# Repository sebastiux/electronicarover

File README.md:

# electronicarover

Electrónica del rover: Raspberry Pi 5 como cerebro, 2× ESP32 esclavas (tracción y servos) y 3× L298N para 6 motores Pololu 37D.

- [`hardware/`](hardware/README.md): PCB portadora en KiCad (esquemático, PCB, footprints propios, generador en Python).
- [`firmware/common/rover_pins.h`](firmware/common/rover_pins.h): mapa de pines de la PCB para el firmware.

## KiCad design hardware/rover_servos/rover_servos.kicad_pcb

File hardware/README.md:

# Rover Controller v1.2: PCB de 2 capas (KiCad)

> **Versión para fresar en casa en 2 tarjetas de una cara (tracción y servos):** ver [`DOS_TARJETAS.md`](DOS_TARJETAS.md). La versión de una sola tarjeta de 2 caras para la Cubiko está en [`cubiko/README.md`](cubiko/README.md).

> **Lista completa de piezas y medidas de pads y barrenos:** [`LISTA_MATERIALES.md`](LISTA_MATERIALES.md).

> **Para entender el circuito:** [`esquema_didactico/`](esquema_didactico/README.md) (4 hojas: alimentación, señales y cada tarjeta por dentro).

PCB de **2 capas** (F.Cu arriba y B.Cu abajo) de 200 × 150 mm. Los módulos se montan encima y la tarjeta los interconecta, así que los únicos cables que salen son los de **batería, motores/encoders, servos y reguladores**.

| Bloque | Módulo | Función |
|---|---|---|
| U1 | **Raspberry Pi 5**, debajo de la PCB con header hembra 2x20 | Cerebro |
| U2 | **ESP32 DevKit V1 30p** (ESP32-A, horizontal) | Tracción: 6 motores + 6 encoders |
| U3 | **ESP32 DevKit V1 30p** (ESP32-B, vertical) | 4 servos de dirección + 4 del brazo (base, hombro, pinza, codo/muñeca), voltaje de batería |
| U4–U6 | **3× L298N (HW-095)** con pines en vez de bornas | 6× Pololu 37D 12V 30:1 |
| J1 | **XT60 macho** | Batería LiPo 3S (Gens Ace 5000 mAh) |
| J3 / J4 / J5 / J6 | Borneras 5.08 mm | 12 V hacia el step-down de 5 V, 12 V hacia el BEC de servos, entrada de 5 V/5 A y entrada de servos a 6 V |
| J11–J16 + J21–J26 | Bornera + header 1x6 (cable Pololu) | Motores y encoders |
| J31–J38 | Header 1x3 (GND, V+, SIG) | Servos |

**Estado:** ruteada al 100 %. DRC de KiCad: **0 violaciones y 0 conexiones pendientes**. Además `tools/check_proto.py` confirma **0 conexiones abiertas sin barrenos metalizados**. Lleva 101 vías de 2.2/1.0 mm.

**Un solo diseño sirve para dos formas de fabricar.** La PCB se diseñó para funcionar sin metalizado; con metalizado (PTH) funciona igual.

| Fabricación | Paquete | Para quién |
|---|---|---|
| **Prototipado CNC** (sin PTH, sin máscara) | `fab/rover_controller_v1.2_prototipado.zip` | Servicio de prototipado de AG Electrónica (1 h a 1 día) |
| **Industrial + ensamble THT** | `fab/rover_controller_v1.2_PCBWay.zip` (detalle en `fab/pcbway/`) | PCBWay, llave en mano: todo soldado menos L298N y Pi |

## Cambios en la v1.2

| Cambio | Por qué |
|---|---|
| **Modo prototipado:** cada pad conecta solo por la cara donde se suelda (abajo; el header de la Pi, arriba). Las pistas de arriba van solo de vía a vía. Las vías son de 2.2/1.0 mm para meter un pin y soldarlo por ambas caras. | El servicio de prototipado no metaliza barrenos. |
| **L298N de 43.9 × 43.9 mm** con barrenos de **Ø4.0 mm a ±18.75 mm**, solo los 2 del lado del disipador | Las fuentes dan separaciones de 36.6, 37, 37.2 y 38.0 mm; un barreno de 4 mm acepta un M3 en cualquier separación entre 36.5 y 38.5 mm. El lado de los pines queda fijo por los 13 pines soldados. |
| GND de los pines 25 y 39 de la Pi con vía propia | Libera la salida del pin 29 (UART2 RX). |
| Pista de 12 V entre U4 y U6 desplazada | Deja lugar a la vía de GND de U5. |

## Cambios en la v1.1 (revisión de diseño)

| Cambio | Por qué |
|---|---|
| Retorno de **GND de potencia de 3 mm**, igual que VBAT | Con 6 motores el retorno puede pasar de 10 A. |
| **1 nF del nodo de cada encoder a GND** (C11–C16) | Junto con los 10k forma un filtro RC de ~7 µs contra el ruido del PWM de los motores. |
| **Schottky 1N5819 en el VIN de cada ESP32** (D5, D6) | Al conectar el USB a la PC, no se retroalimenta el +5 V de la Pi ni el puerto USB. |

| Corriente máx. aprox. (IPC-2221, +20 °C, cobre externo) | 1 oz | 2 oz |
|---|---|---|
| 3.0 mm: VBAT y GND de potencia | 7.2 A | 11.9 A |
| 2.0 mm: motores y +5V | 5.4 A | 8.9 A |

**Tierra común:** existe una sola red `GND` que une batería, L298N, Pi, ESP32, servos y encoders, con plano de GND relleno en la cara inferior.

## Fabricación A: prototipado CNC (sin metalizado)

Sube `fab/rover_controller_v1.2_prototipado.zip`: cobre superior, cobre inferior, contorno y **un solo archivo de taladros**. También incluye `vias_pines.csv` con la posición de cada vía-pin.

1. Pide **2 caras, sin máscara ni serigrafía**. Si es posible, usa placa con cobre de 2 oz (o estaña las pistas de potencia).
2. **Vías-pin (101):** mete un pin de header (o un alambre de 0.8–0.9 mm) en cada vía y **suéldalo arriba y abajo**. Hazlo **antes** de montar los L298N y las ESP32, porque algunas quedan debajo. Corta los pines a ras.
3. **Componentes:** todos van arriba y se sueldan **por abajo**. La única excepción es el **header 2x20 de la Pi**: va abajo y se suelda **por arriba**.
4. Revisa continuidad de 12 V, 5 V, 6 V y GND contra GND (no debe haber corto) antes de conectar módulos.
5. Para guiarte al soldar: `docs/cobre_superior_FCu_1a1.pdf`, `docs/cobre_inferior_BCu_espejo_1a1.pdf` y `docs/plantilla_1a1.pdf`.

## Fabricación B: PCBWay (PCB + ensamble llave en mano)

Todo en `fab/pcbway/`. La hoja **`cotizacion_PCBWay_rover_v1.2.png`** trae los valores exactos de los formularios.

| Archivo | Uso |
|---|---|
| `rover_controller_v1.2_gerbers_PCBWay.zip` | Gerbers con máscara y serigrafía + taladros PTH/NPTH |
| `rover_controller_BOM_PCBWay.xlsx` / `.csv` | 24 números de parte, 70 piezas. U4–U6 marcados DNP. |
| `rover_controller_centroides.csv` | Posición y rotación de cada componente |
| `plano_montaje_superior.pdf`, `plano_montaje_inferior_espejo.pdf` | Planos de montaje |

- **PCB:** 2 capas, FR-4 1.6 mm, **cobre de 2 oz**, HASL sin plomo, máscara verde.
- **Ensamble:** turnkey THT por las dos caras: todo arriba, más el header 2x20 de la Pi abajo.
- **No se sueldan:** los L298N (los instalas tú), la Raspberry Pi 5 y las ESP32. De las ESP32 solo se sueldan sus zócalos 1x15.
- Si cambias componentes, vuelve a generar el BOM con `python3 tools/bom_pcbway.py`.

**Barrenos de montaje al chasis:** 8 M3 en las orillas (H1–H8), más los 4 M2.5 de la Raspberry Pi.

## Estructura

```
hardware/
├── rover_controller/          Proyecto KiCad (abrir rover_controller.kicad_pro)
│   ├── rover.kicad_sym / rover.pretty/   símbolos y footprints propios
│   └── bom.csv                lista de materiales
├── tools/
│   ├── rover_design.py        FUENTE DE VERDAD: pines, redes, posiciones, cotas, guías de ruteo
│   ├── generate.py            genera el esquemático y la PCB (--route: rutea)
│   ├── router1l.py            ruteador (2 capas; LAYERS = 1 en rover_design.py para una capa con puentes)
│   ├── fix_proto.py           cierre puntual de pendientes (quitar/agregar pistas y re-rutear redes)
│   ├── cierre_v1.2.sh         registro de los cierres hechos en la v1.2
│   ├── check_proto.py         verifica conectividad SIN barrenos metalizados
│   ├── bom_pcbway.py          BOM para ensamble llave en mano
│   └── export_fab.sh          paquetes de prototipado y PCBWay, PDFs 1:1 e imágenes
└── docs/
firmware/common/rover_pins.h   mapa de pines para el firmware
```

Para regenerar, usa el Python de KiCad 7 o posterior con `numpy` y `scipy` instalados. El ruteo es determinista y tarda unos 25 minutos. En la v1.2 dejó 6 pads pendientes, que se cerraron con `tools/fix_proto.py` (los comandos están en `tools/cierre_v1.2.sh`). Sin `--route` el script no sobrescribe una PCB ya ruteada.

```bash
python3 hardware/tools/generate.py --route
```

```bash
hardware/tools/export_fab.sh
```

## Antes de fabricar: verifica las cotas

**L298N:** el footprint usa el plano de tu módulo (43.9 × 43.9 mm, barrenos a 38.0 mm). Las fuentes no coinciden (36.6 / 37 / 37.2 / 38 mm) y ninguna da la posición de los pines. **Imprime `docs/plantilla_1a1.pdf` al 100 %** y pon encima un L298N sin bornas, las ESP32 y la Pi. Si un pin no coincide, corrige el diccionario `L298N`, `ESP32` o `RPI` en `rover_design.py` y vuelve a generar.

La fila doble de pads de cada ESP32 acepta clones con 25.4 o 22.86 mm entre filas.

## Montaje

### L298N

1. Desuelda las 3 bornas azules y el header 1x6 (`ENA IN1 IN2 IN3 IN4 ENB`).
2. **Quita los jumpers ENA/ENB.** En la PCB van a `MOTOR_EN`.
3. **Deja puesto el jumper 5V-EN.** El regulador 78M05 del módulo alimenta su lógica, y su pin **+5V alimenta los dos encoders** de ese módulo.
4. Suelda header macho por arriba del módulo, con los pines saliendo por abajo, en las 7 posiciones de potencia y las 6 lógicas.
5. Atornilla el lado del disipador con 2 standoffs M3 (barrenos de 4 mm en la PCB) y suelda los 13 pines por abajo.

### Raspberry Pi 5

1. Suelda un **header hembra 2x20** en la **cara inferior**; los pines se sueldan por arriba.
2. Si quieres acceder por arriba a los GPIO libres, usa en su lugar un **stacking header** de pines largos: los pines sobresalen sobre la PCB y ahí conectas cables Dupont.
3. Monta la Pi debajo con standoffs M2.5: 11 mm, o 16–18 mm con el Active Cooler.

### ESP32

Van sobre headers hembra 1x15, así que se pueden quitar.

- **ESP32-A** va horizontal, con la antena a la izquierda y el USB a la derecha.
- **ESP32-B** va vertical, con la antena arriba y el USB abajo.

## Arquitectura eléctrica

```
Batería 3S (XT60) ─► F1 15 A ─► VBAT_F ─┬─► L298N +12V (x3)
                                         ├─► J3 ─► step-down 5V/5A ─► J5 ─► +5V (Pi 5, ESP32)
                                         └─► J4 ─► BEC 6V ≥10A ─────► J6 ─► SERVO_V (8 servos)
L298N (regulador 78M05 del módulo) ─► +5V de los encoders de sus 2 motores
```

- **Pi 5 por GPIO:** en `/boot/firmware/config.txt` agrega `usb_max_current_enable=1`. Además corre `sudo rpi-eeprom-config -e` y pon `PSU_MAX_CURRENT=5000`. Para proteger la Pi hay un TVS SA5.0A (D1) y 1000 µF (C2).
- **UART sin cables:** la Pi tiene UART2 (GPIO4/5, `/dev/ttyAMA2`) hacia la ESP32-A y UART0 (GPIO14/15, `/dev/ttyAMA0`) hacia la ESP32-B, con 1k en serie. Activa `dtoverlay=uart2-pi5` y `dtoverlay=uart0-pi5`.
- **Asignación de pines** (ver `firmware/common/rover_pins.h`): está pensada para que el ruteo quede limpio.
  - En la ESP32-A, los IN1–IN4 de los tres L298N siguen el mismo orden que la fila de pines, así que las pistas bajan en abanico sin cruzarse.
  - En la ESP32-B, cada servo queda a la misma altura que su GPIO.
- **`MOTOR_EN`** (IO13 de la ESP32-A, con pull-down) habilita los 6 canales. Los motores no se mueven mientras arranca la ESP32.
- **Encoders:** solo el canal A, con divisor 10k/20k de 5 V a 3.3 V.
- **Batería:** IO34 de la ESP32-B, con divisor 100k/27k. Si la LiPo baja de 3.3 V por celda (9.9 V), la ESP32-B se lo avisa a la Pi con una bandera en su telemetría (`B mv 1`). El firmware no corta los motores por sí solo: esa decisión se programa en la Pi.

### Componentes discretos

- Resistencias de **1/4 W** de orificio pasante.
- **LEDs de 5 mm:** D2 rojo (12 V), D3 verde (5 V) y D4 azul (servos).
- Electrolíticos radiales, TVS en encapsulado DO-15 y portafusible ATO.

## ⚠️ Limitaciones

1. **L298N vs. Pololu 37D:** el motor pide hasta **5.5 A** cuando se bloquea y el L298N soporta unos 2 A continuos por canal. Además pierde 2–3 V. Usa rampas de PWM y detecta bloqueos con el encoder.
2. **ESP32-A:** GPIO1 (TX0) maneja un IN del L298N. No uses `Serial.print()` mientras controlas los motores; para telemetría usa `Serial2` hacia la Pi.
3. No hay protección contra polaridad inversa. Respeta la polaridad del XT60: lado recto = +, lado biselado = −.

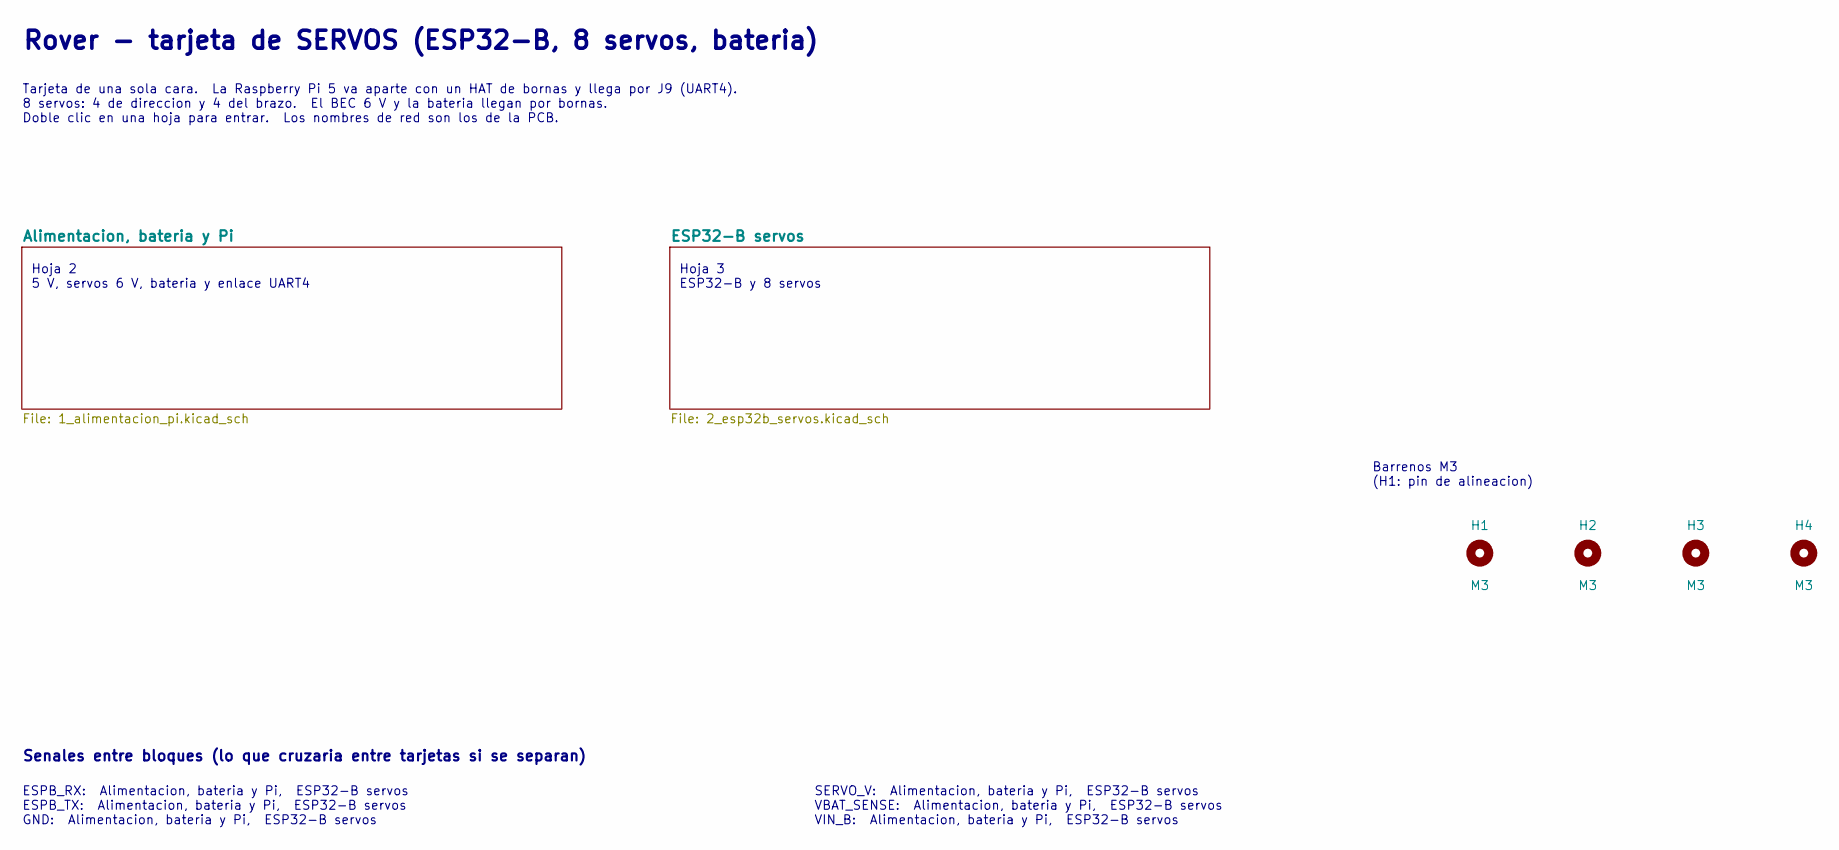
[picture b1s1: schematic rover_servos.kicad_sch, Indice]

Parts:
H1, H2, H3, H4: M3; MountingHole_3.2mm_M3; MPN M3

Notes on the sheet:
Hoja 2 5 V, servos 6 V, bateria y enlace UART4
Hoja 3 ESP32-B y 8 servos
Barrenos M3 (H1: pin de alineacion)
Rover - tarjeta de SERVOS (ESP32-B, 8 servos, bateria)
Tarjeta de una sola cara. La Raspberry Pi 5 va aparte con un HAT de bornas y llega por J9 (UART4). 8 servos: 4 de direccion y 4 del brazo. El BEC 6 V y la bateria llegan por bornas. Doble clic en una hoja para entrar. Los nombres de red son los de la PCB.
Senales entre bloques (lo que cruzaria entre tarjetas si se separan)
ESPB_RX: Alimentacion, bateria y Pi, ESP32-B servos ESPB_TX: Alimentacion, bateria y Pi, ESP32-B servos GND: Alimentacion, bateria y Pi, ESP32-B servos
SERVO_V: Alimentacion, bateria y Pi, ESP32-B servos VBAT_SENSE: Alimentacion, bateria y Pi, ESP32-B servos VIN_B: Alimentacion, bateria y Pi, ESP32-B servos

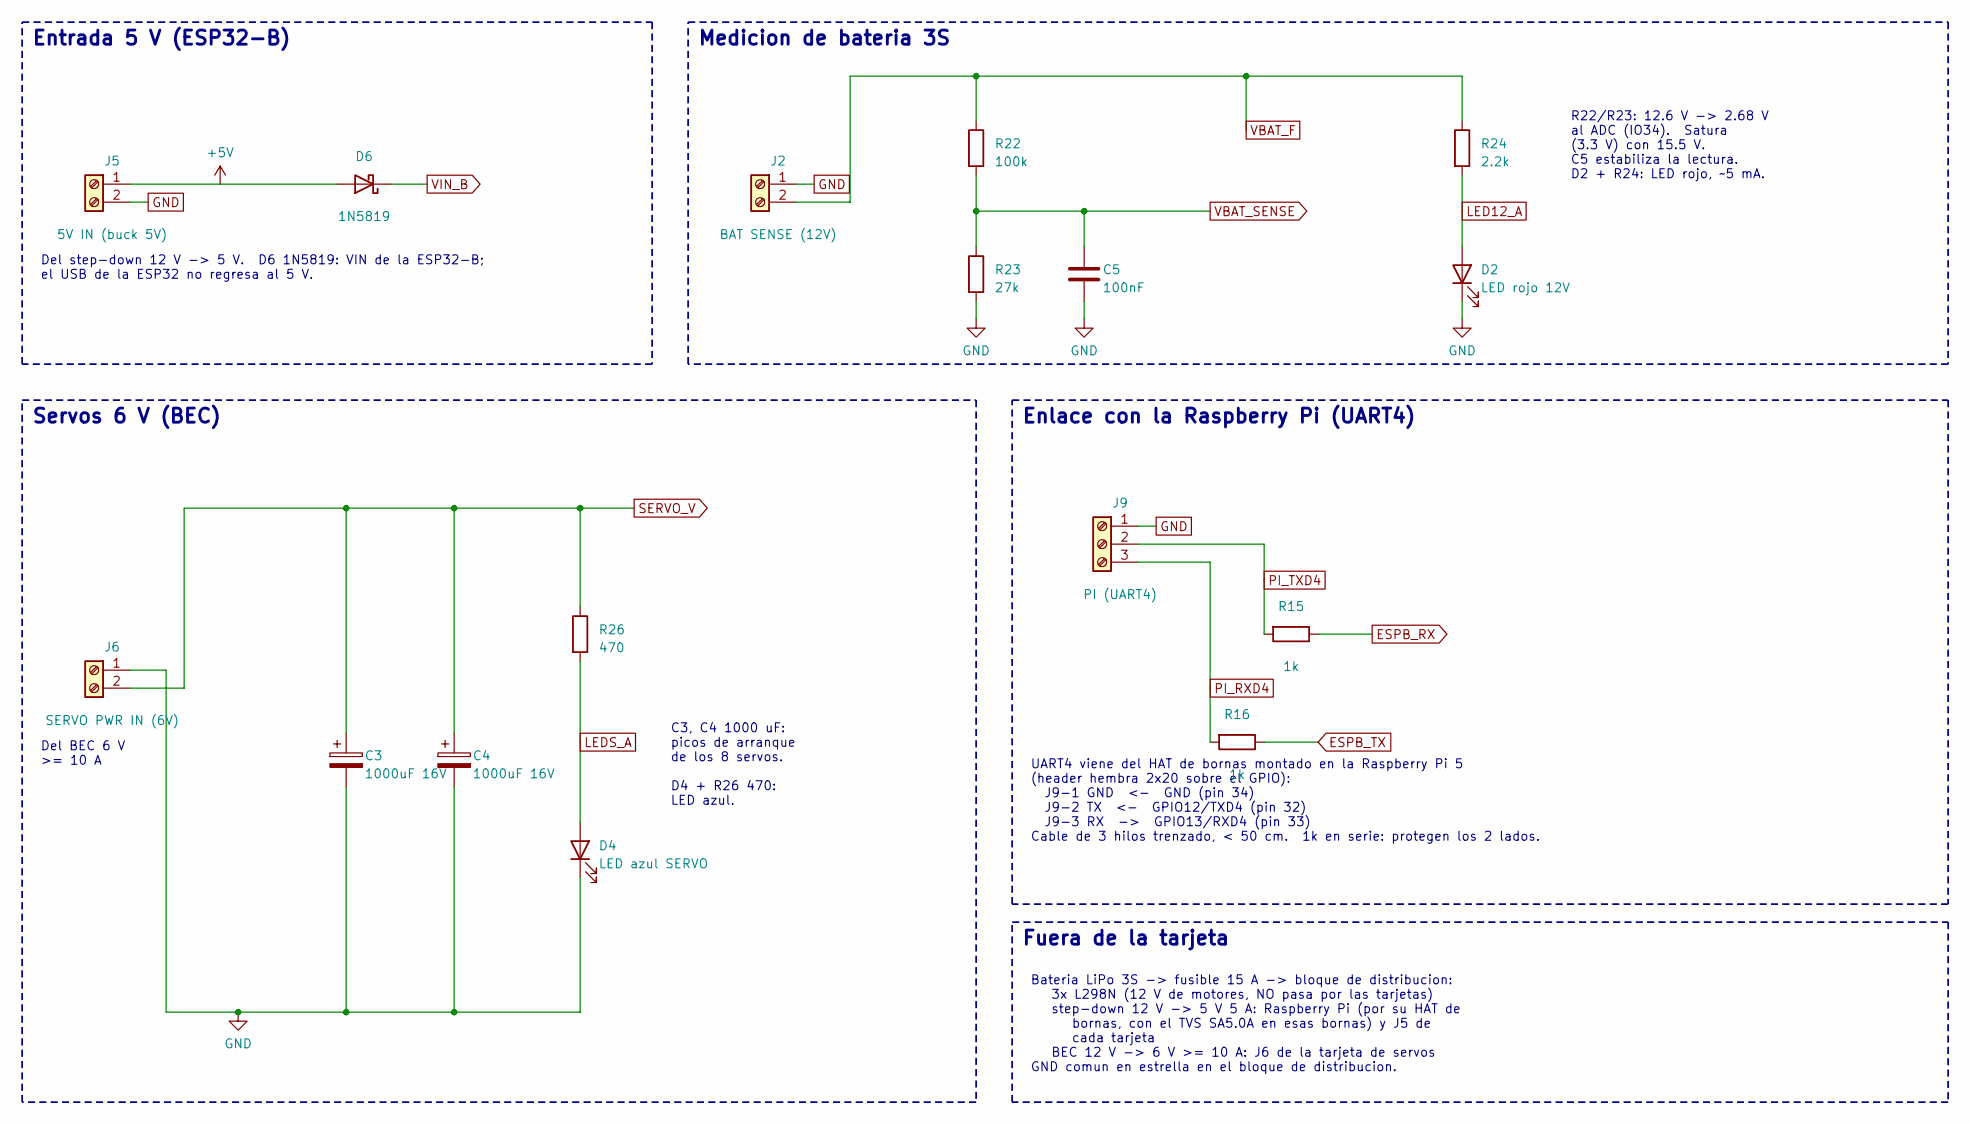
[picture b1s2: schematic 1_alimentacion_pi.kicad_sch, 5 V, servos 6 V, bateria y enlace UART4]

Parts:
C3, C4: 1000uF 16V; CP_Radial_D10.0mm_P5.00mm; MPN 1000uF 16V radial, cuerpo de 10 mm de d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
C5: 100nF; C_Disc_D5.0mm_W2.5mm_P5.00mm; MPN 100nF
D2: LED rojo 12V; LED_D5.0mm; MPN LED 5mm THT tradicional (rojo)
D4: LED azul SERVO; LED_D5.0mm; MPN LED 5mm THT tradicional (azul)
D6: 1N5819; D_DO-41_SOD81_P10.16mm_Horizontal; MPN 1N5819 DO-41
J2: BAT SENSE (12V); TerminalBlock_Phoenix_MKDS-1,5-2-5.08_1x02_P5.08mm_Horizont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; MPN Phoenix MKDS 1,5/2-5,08 o KF301-2P
J5: 5V IN (buck 5V); TerminalBlock_Phoenix_MKDS-1,5-2-5.08_1x02_P5.08mm_Horizont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; MPN Phoenix MKDS 1,5/2-5,08 o KF301-2P
J6: SERVO PWR IN (6V); TerminalBlock_Phoenix_MKDS-1,5-2-5.08_1x02_P5.08mm_Horizont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; MPN Phoenix MKDS 1,5/2-5,08 o KF301-2P
J9: PI (UART4); TerminalBlock_Phoenix_PT-1,5-3-3.5-H_1x03_P3.50mm_Horizontal; MPN Phoenix PT 1,5/3-3,5-H o KF350-3P 3.5mm
R15, R16: 1k; R_Axial_DIN0207_L6.3mm_D2.5mm_P7.62mm_Horizontal; MPN Resistencia 1k 1/4W (0.25W) THT pelicul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
R22: 100k; R_Axial_DIN0207_L6.3mm_D2.5mm_P7.62mm_Horizontal; MPN Resistencia 100k 1/4W (0.25W) THT pelic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
R23: 27k; R_Axial_DIN0207_L6.3mm_D2.5mm_P7.62mm_Horizontal; MPN Resistencia 27k 1/4W (0.25W) THT pelicu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
R24: 2.2k; R_Axial_DIN0207_L6.3mm_D2.5mm_P7.62mm_Horizontal; MPN Resistencia 2.2k 1/4W (0.25W) THT pelic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
R26: 470; R_Axial_DIN0207_L6.3mm_D2.5mm_P7.62mm_Horizontal; MPN Resistencia 470 1/4W (0.25W) THT pelicu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

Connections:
+5V: D6.2 (A), J5.1
ESPB_RX: R15.1; also elsewhere on the board
ESPB_TX: R16.1; also elsewhere on the board
GND: C3.2, C4.2, C5.2, D2.1 (K), D4.1 (K), J2.1, J5.2, J6.1, J9.1, R23.2; also elsewhere on the board
LED12_A: D2.2 (A), R24.2
LEDS_A: D4.2 (A), R26.2
PI_RXD4: J9.3, R16.2
PI_TXD4: J9.2, R15.2
SERVO_V: C3.1, C4.1, J6.2, R26.1; also elsewhere on the board
VBAT_F: J2.2, R22.1, R24.1
VBAT_SENSE: C5.1, R22.2, R23.1; also elsewhere on the board
VIN_B: D6.1 (K); also elsewhere on the board

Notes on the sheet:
Entrada 5 V (ESP32-B)
Del step-down 12 V -> 5 V. D6 1N5819: VIN de la ESP32-B; el USB de la ESP32 no regresa al 5 V.
Servos 6 V (BEC)
Del BEC 6 V >= 10 A
C3, C4 1000 uF: picos de arranque de los 8 servos. D4 + R26 470: LED azul.
Medicion de bateria 3S
R22/R23: 12.6 V -> 2.68 V al ADC (IO34). Satura (3.3 V) con 15.5 V. C5 estabiliza la lectura. D2 + R24: LED rojo, ~5 mA.
Enlace con la Raspberry Pi (UART4)
UART4 viene del HAT de bornas montado en la Raspberry Pi 5 (header hembra 2x20 sobre el GPIO): J9-1 GND <- GND (pin 34) J9-2 TX <- GPIO12/TXD4 (pin 32) J9-3 RX -> GPIO13/RXD4 (pin 33) Cable de 3 hilos trenzado, < 50 cm. 1k en serie: protegen los 2 lados.
Fuera de la tarjeta
Bateria LiPo 3S -> fusible 15 A -> bloque de distribucion: 3x L298N (12 V de motores, NO pasa por las tarjetas) step-down 12 V -> 5 V 5 A: Raspberry Pi (por su HAT de bornas, con el TVS SA5.0A en esas bornas) y J5 de cada tarjeta BEC 12 V -> 6 V >= 10 A: J6 de la tarjeta de servos GND comun en estr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

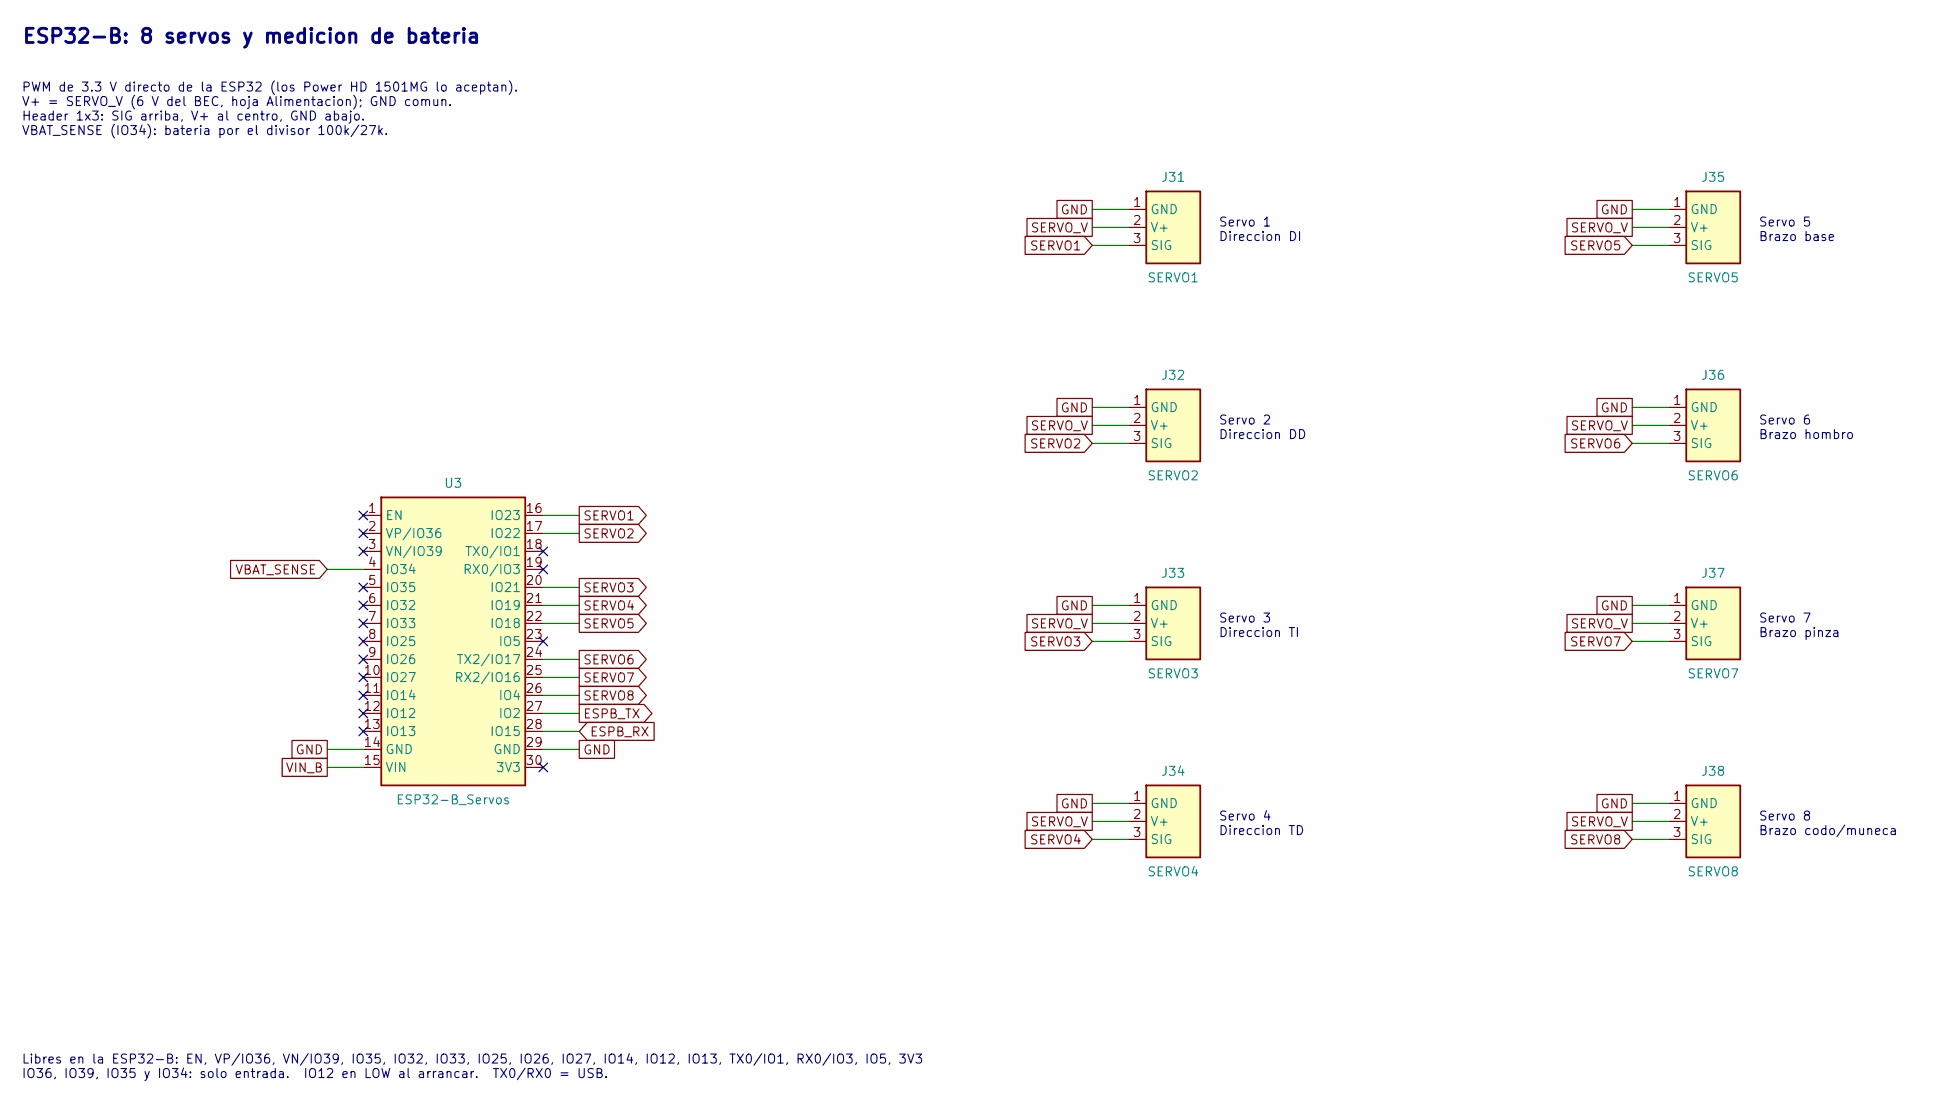
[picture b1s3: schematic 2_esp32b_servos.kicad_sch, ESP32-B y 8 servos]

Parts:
J31: SERVO1; Servo_Header_1x03; MPN Header macho 1x3 2.54mm
J32: SERVO2; Servo_Header_1x03; MPN Header macho 1x3 2.54mm
J33: SERVO3; Servo_Header_1x03; MPN Header macho 1x3 2.54mm
J34: SERVO4; Servo_Header_1x03; MPN Header macho 1x3 2.54mm
J35: SERVO5; Servo_Header_1x03; MPN Header macho 1x3 2.54mm
J36: SERVO6; Servo_Header_1x03; MPN Header macho 1x3 2.54mm
J37: SERVO7; Servo_Header_1x03; MPN Header macho 1x3 2.54mm
J38: SERVO8; Servo_Header_1x03; MPN Header macho 1x3 2.54mm
U3: ESP32-B_Servos; ESP32_DevKitV1_30P_1x15; MPN ESP32 DevKit V1 + 2x header hembra 1x15

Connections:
ESPB_RX: U3.28 (IO15); also elsewhere on the board
ESPB_TX: U3.27 (IO2); also elsewhere on the board
GND: J31.1 (GND), J32.1 (GND), J33.1 (GND), J34.1 (GND), J35.1 (GND), J36.1 (GND), J37.1 (GND), J38.1 (GND), U3.14 (GND), U3.29 (GND); also elsewhere on the board
SERVO1: J31.3 (SIG), U3.16 (IO23)
SERVO2: J32.3 (SIG), U3.17 (IO22)
SERVO3: J33.3 (SIG), U3.20 (IO21)
SERVO4: J34.3 (SIG), U3.21 (IO19)
SERVO5: J35.3 (SIG), U3.22 (IO18)
SERVO6: J36.3 (SIG), U3.24 (TX2/IO17)
SERVO7: J37.3 (SIG), U3.25 (RX2/IO16)
SERVO8: J38.3 (SIG), U3.26 (IO4)
SERVO_V: J31.2 (V+), J32.2 (V+), J33.2 (V+), J34.2 (V+), J35.2 (V+), J36.2 (V+), J37.2 (V+), J38.2 (V+); also elsewhere on the board
VBAT_SENSE: U3.4 (IO34); also elsewhere on the board
VIN_B: U3.15 (VIN); also elsewhere on the board

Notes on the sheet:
Servo 1 Direccion DI
Servo 2 Direccion DD
Servo 3 Direccion TI
Servo 4 Direccion TD
Servo 5 Brazo base
Servo 6 Brazo hombro
Servo 7 Brazo pinza
Servo 8 Brazo codo/muneca
ESP32-B: 8 servos y medicion de bateria
PWM de 3.3 V directo de la ESP32 (los Power HD 1501MG lo aceptan). V+ = SERVO_V (6 V del BEC, hoja Alimentacion); GND comun. Header 1x3: SIG arriba, V+ al centro, GND abajo. VBAT_SENSE (IO34): bateria por el divisor 100k/27k.
Libres en la ESP32-B: EN, VP/IO36, VN/IO39, IO35, IO32, IO33, IO25, IO26, IO27, IO14, IO12, IO13, TX0/IO1, RX0/IO3, IO5, 3V3 IO36, IO39, IO35 y IO34: solo entrada. IO12 en LOW al arrancar. TX0/RX0 = USB.

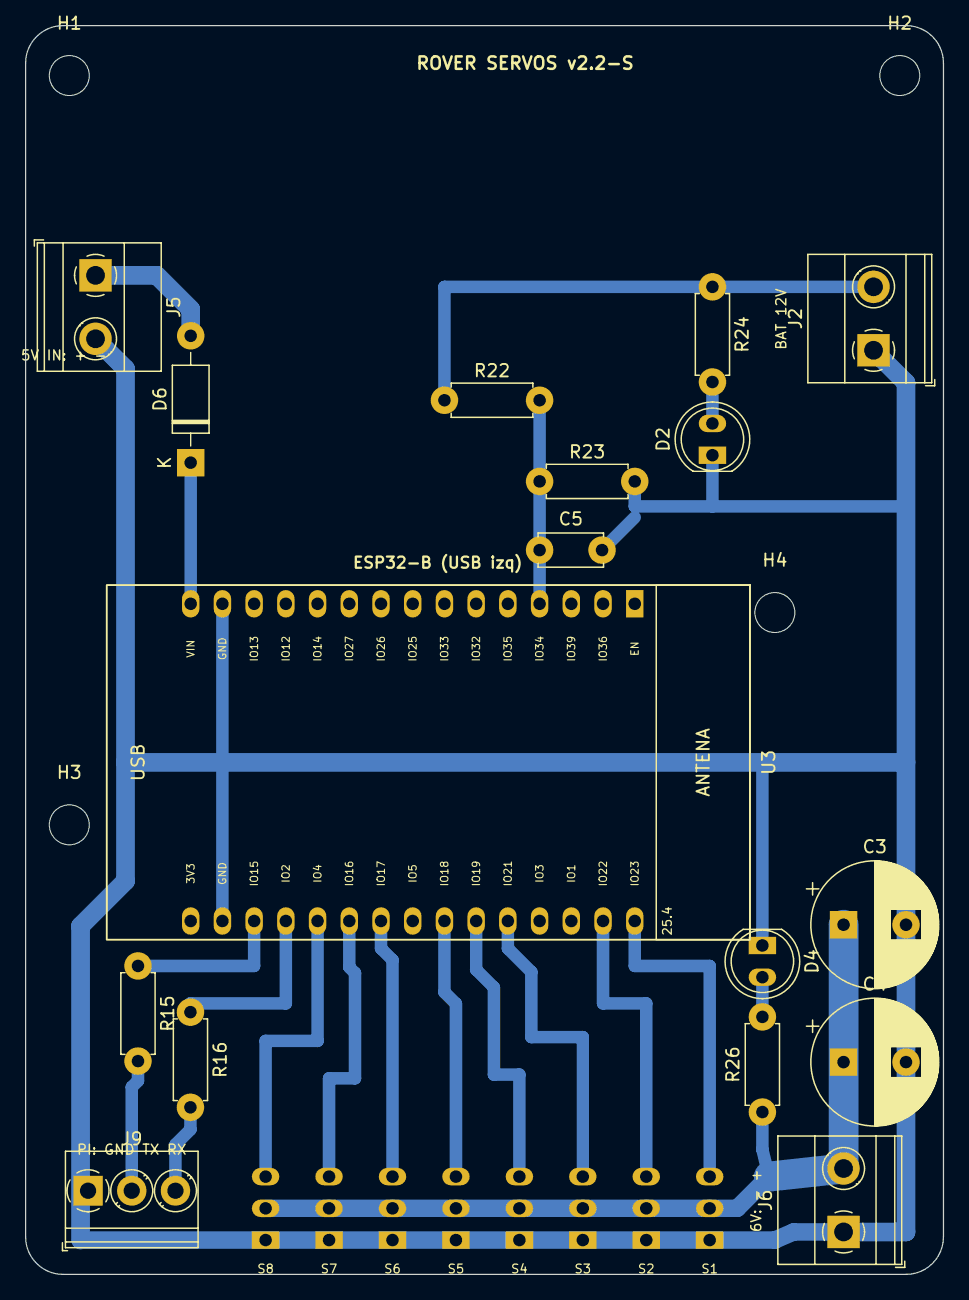
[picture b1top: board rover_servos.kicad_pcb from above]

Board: 2 copper layers, 73.5 x 100.0 mm, 29 parts (0 on the bottom side), 20 nets.

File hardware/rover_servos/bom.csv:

Cant;Referencias;Valor;Footprint;Parte sugerida;Descripcion
2;C3,C4;1000uF 10V;Capacitor_THT:CP_Radial_D10.0mm_P5.00mm;1000uF 10V;Bulk servos
1;C5;100nF;Capacitor_THT:C_Disc_D5.0mm_W2.5mm_P5.00mm;100nF;Filtro ADC VBAT
1;D2;LED rojo 12V;LED_THT:LED_D5.0mm;LED 5mm THT tradicional (rojo);Indicador bateria
1;D4;LED azul SERVO;LED_THT:LED_D5.0mm;LED 5mm THT tradicional (azul);Indicador rail servos
1;D6;1N5819;Diode_THT:D_DO-41_SOD81_P10.16mm_Horizontal;1N5819 DO-41;Schottky +5V -> VIN ESP32-B
4;H1,H2,H3,H4;M3;MountingHole:MountingHole_3.2mm_M3;M3;Agujero de montaje M3
1;J2;BAT SENSE (12V);TerminalBlock_Phoenix:TerminalBlock_Phoenix_MKDS-1,5-2-5.08_1x02_P5.08mm_Horizontal;Phoenix MKDS 1,5/2-5,08 o KF301-2P;Derivacion de bateria despues del fusible (solo medicion y LED, < 10 mA)
1;J31;SERVO1;rover:Servo_Header_1x03;Header macho 1x3 2.54mm;Servo 1 - Direccion DI (SIG arriba, GND abajo)
1;J32;SERVO2;rover:Servo_Header_1x03;Header macho 1x3 2.54mm;Servo 2 - Direccion DD (SIG arriba, GND abajo)
1;J33;SERVO3;rover:Servo_Header_1x03;Header macho 1x3 2.54mm;Servo 3 - Direccion TI (SIG arriba, GND abajo)
1;J34;SERVO4;rover:Servo_Header_1x03;Header macho 1x3 2.54mm;Servo 4 - Direccion TD (SIG arriba, GND abajo)
1;J35;SERVO5;rover:Servo_Header_1x03;Header macho 1x3 2.54mm;Servo 5 - Brazo base (SIG arriba, GND abajo)
1;J36;SERVO6;rover:Servo_Header_1x03;Header macho 1x3 2.54mm;Servo 6 - Brazo hombro (SIG arriba, GND abajo)
1;J37;SERVO7;rover:Servo_Header_1x03;Header macho 1x3 2.54mm;Servo 7 - Brazo pinza (SIG arriba, GND abajo)
1;J38;SERVO8;rover:Servo_Header_1x03;Header macho 1x3 2.54mm;Servo 8 - Brazo codo/muneca (SIG arriba, GND abajo)
1;J5;5V IN (buck 5V);TerminalBlock_Phoenix:TerminalBlock_Phoenix_MKDS-1,5-2-5.08_1x02_P5.08mm_Horizontal;Phoenix MKDS 1,5/2-5,08 o KF301-2P;Entrada 5 V desde el step-down (ESP32-B)
1;J6;SERVO PWR IN (6V);TerminalBlock_Phoenix:TerminalBlock_Phoenix_MKDS-1,5-2-5.08_1x02_P5.08mm_Horizontal;Phoenix MKDS 1,5/2-5,08 o KF301-2P;Entrada BEC servos 6V
1;J9;PI (UART4);TerminalBlock_Phoenix:TerminalBlock_Phoenix_PT-1,5-3-3.5-H_1x03_P3.50mm_Horizontal;Phoenix PT 1,5/3-3,5-H o KF350-3P 3.5mm;Hacia el HAT de bornas de la Pi: 1 GND (pin 34), 2 TXD4 = GPIO12 (pin 32), 3 RXD4 = GPIO13 (pin 33)
2;R15,R16;1k;Resistor_THT:R_Axial_DIN0207_L6.3mm_D2.5mm_P2.54mm_Vertical;Resistencia 1k 1/4W (0.25W) THT pelicula metalica/carbon;Serie UART Pi TXD4 (GPIO12) -> ESP32-B RX
1;R22;100k;Resistor_THT:R_Axial_DIN0207_L6.3mm_D2.5mm_P7.62mm_Horizontal;Resistencia 100k 1/4W (0.25W) THT pelicula metalica/carbon;Divisor VBAT (alto)
1;R23;27k;Resistor_THT:R_Axial_DIN0207_L6.3mm_D2.5mm_P7.62mm_Horizontal;Resistencia 27k 1/4W (0.25W) THT pelicula metalica/carbon;Divisor VBAT (bajo)
1;R24;2.2k;Resistor_THT:R_Axial_DIN0207_L6.3mm_D2.5mm_P7.62mm_Horizontal;Resistencia 2.2k 1/4W (0.25W) THT pelicula metalica/carbon;Resistencia LED 12V
1;R26;470;Resistor_THT:R_Axial_DIN0207_L6.3mm_D2.5mm_P7.62mm_Horizontal;Resistencia 470 1/4W (0.25W) THT pelicula metalica/carbon;Resistencia LED servos
1;U3;ESP32-B_Servos;rover:ESP32_DevKitV1_30P_DualPitch;ESP32 DevKit V1 + 2x header hembra 1x15;ESP32 DevKit V1 30 pines sobre 2x header hembra 1x15

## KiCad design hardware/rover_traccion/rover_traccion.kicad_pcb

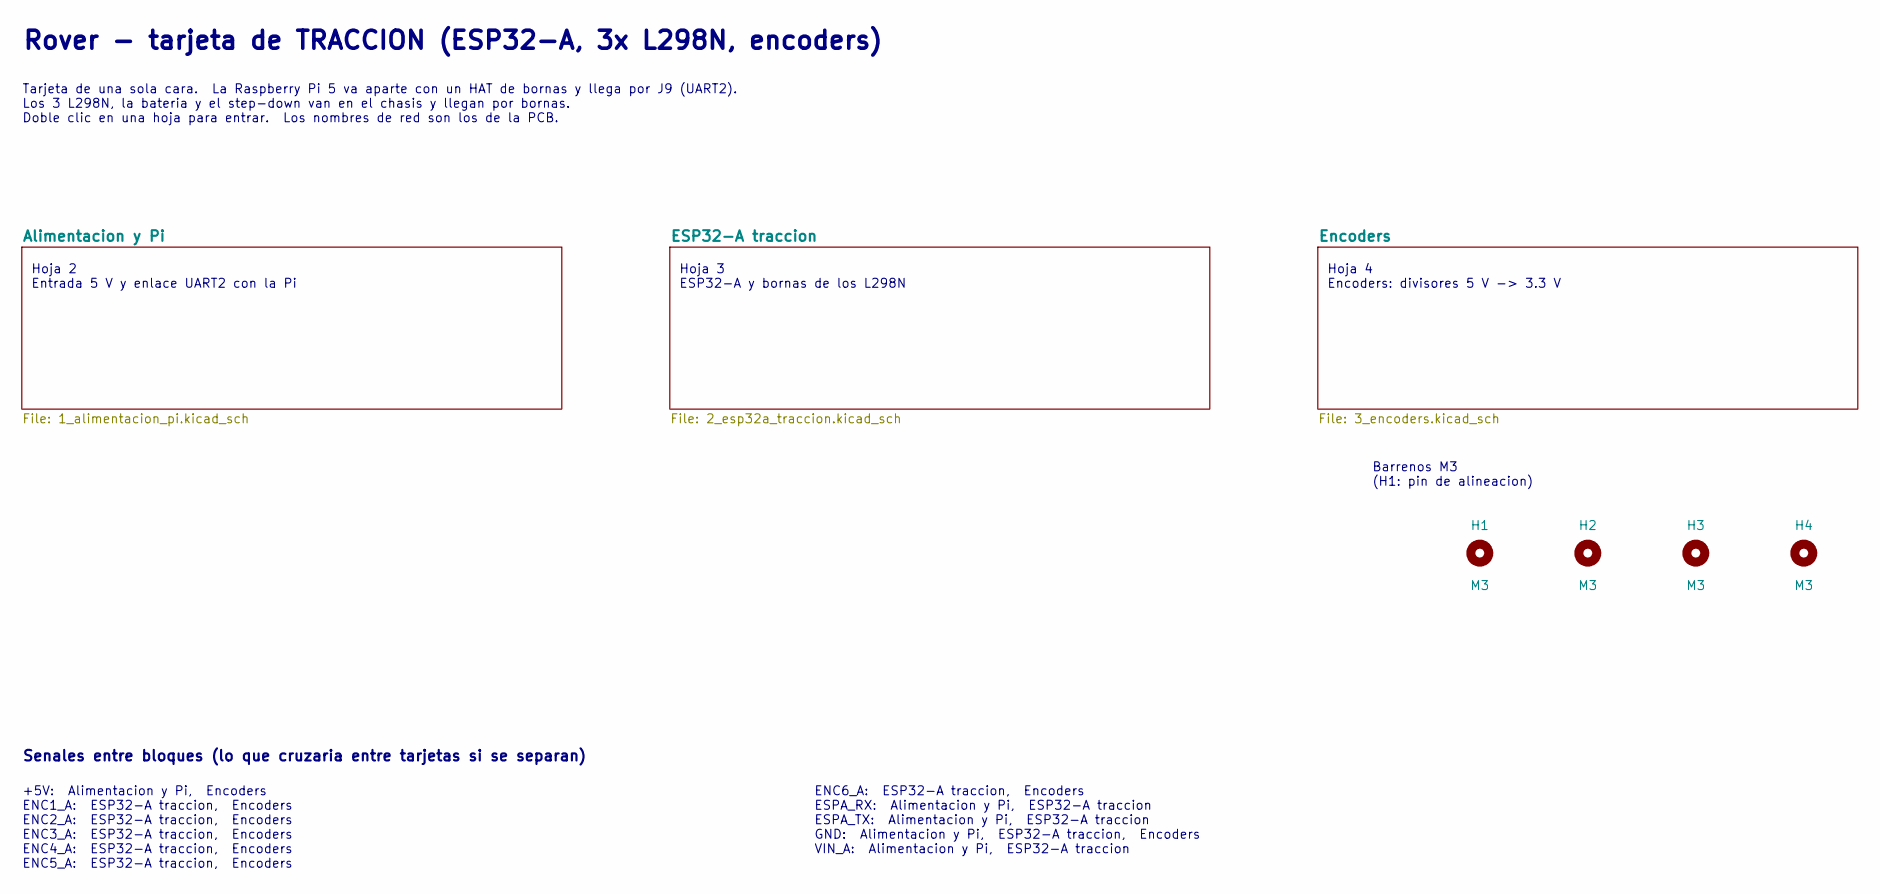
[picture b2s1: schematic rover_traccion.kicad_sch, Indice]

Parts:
H1, H2, H3, H4: M3; MountingHole_3.2mm_M3; MPN M3

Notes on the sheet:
Hoja 2 Entrada 5 V y enlace UART2 con la Pi
Hoja 3 ESP32-A y bornas de los L298N
Hoja 4 Encoders: divisores 5 V -> 3.3 V
Barrenos M3 (H1: pin de alineacion)
Rover - tarjeta de TRACCION (ESP32-A, 3x L298N, encoders)
Tarjeta de una sola cara. La Raspberry Pi 5 va aparte con un HAT de bornas y llega por J9 (UART2). Los 3 L298N, la bateria y el step-down van en el chasis y llegan por bornas. Doble clic en una hoja para entrar. Los nombres de red son los de la PCB.
Senales entre bloques (lo que cruzaria entre tarjetas si se separan)
+5V: Alimentacion y Pi, Encoders ENC1_A: ESP32-A traccion, Encoders ENC2_A: ESP32-A traccion, Encoders ENC3_A: ESP32-A traccion, Encoders ENC4_A: ESP32-A traccion, Encoders ENC5_A: ESP32-A traccion, Encoders
ENC6_A: ESP32-A traccion, Encoders ESPA_RX: Alimentacion y Pi, ESP32-A traccion ESPA_TX: Alimentacion y Pi, ESP32-A traccion GND: Alimentacion y Pi, ESP32-A traccion, Encoders VIN_A: Alimentacion y Pi, ESP32-A traccion

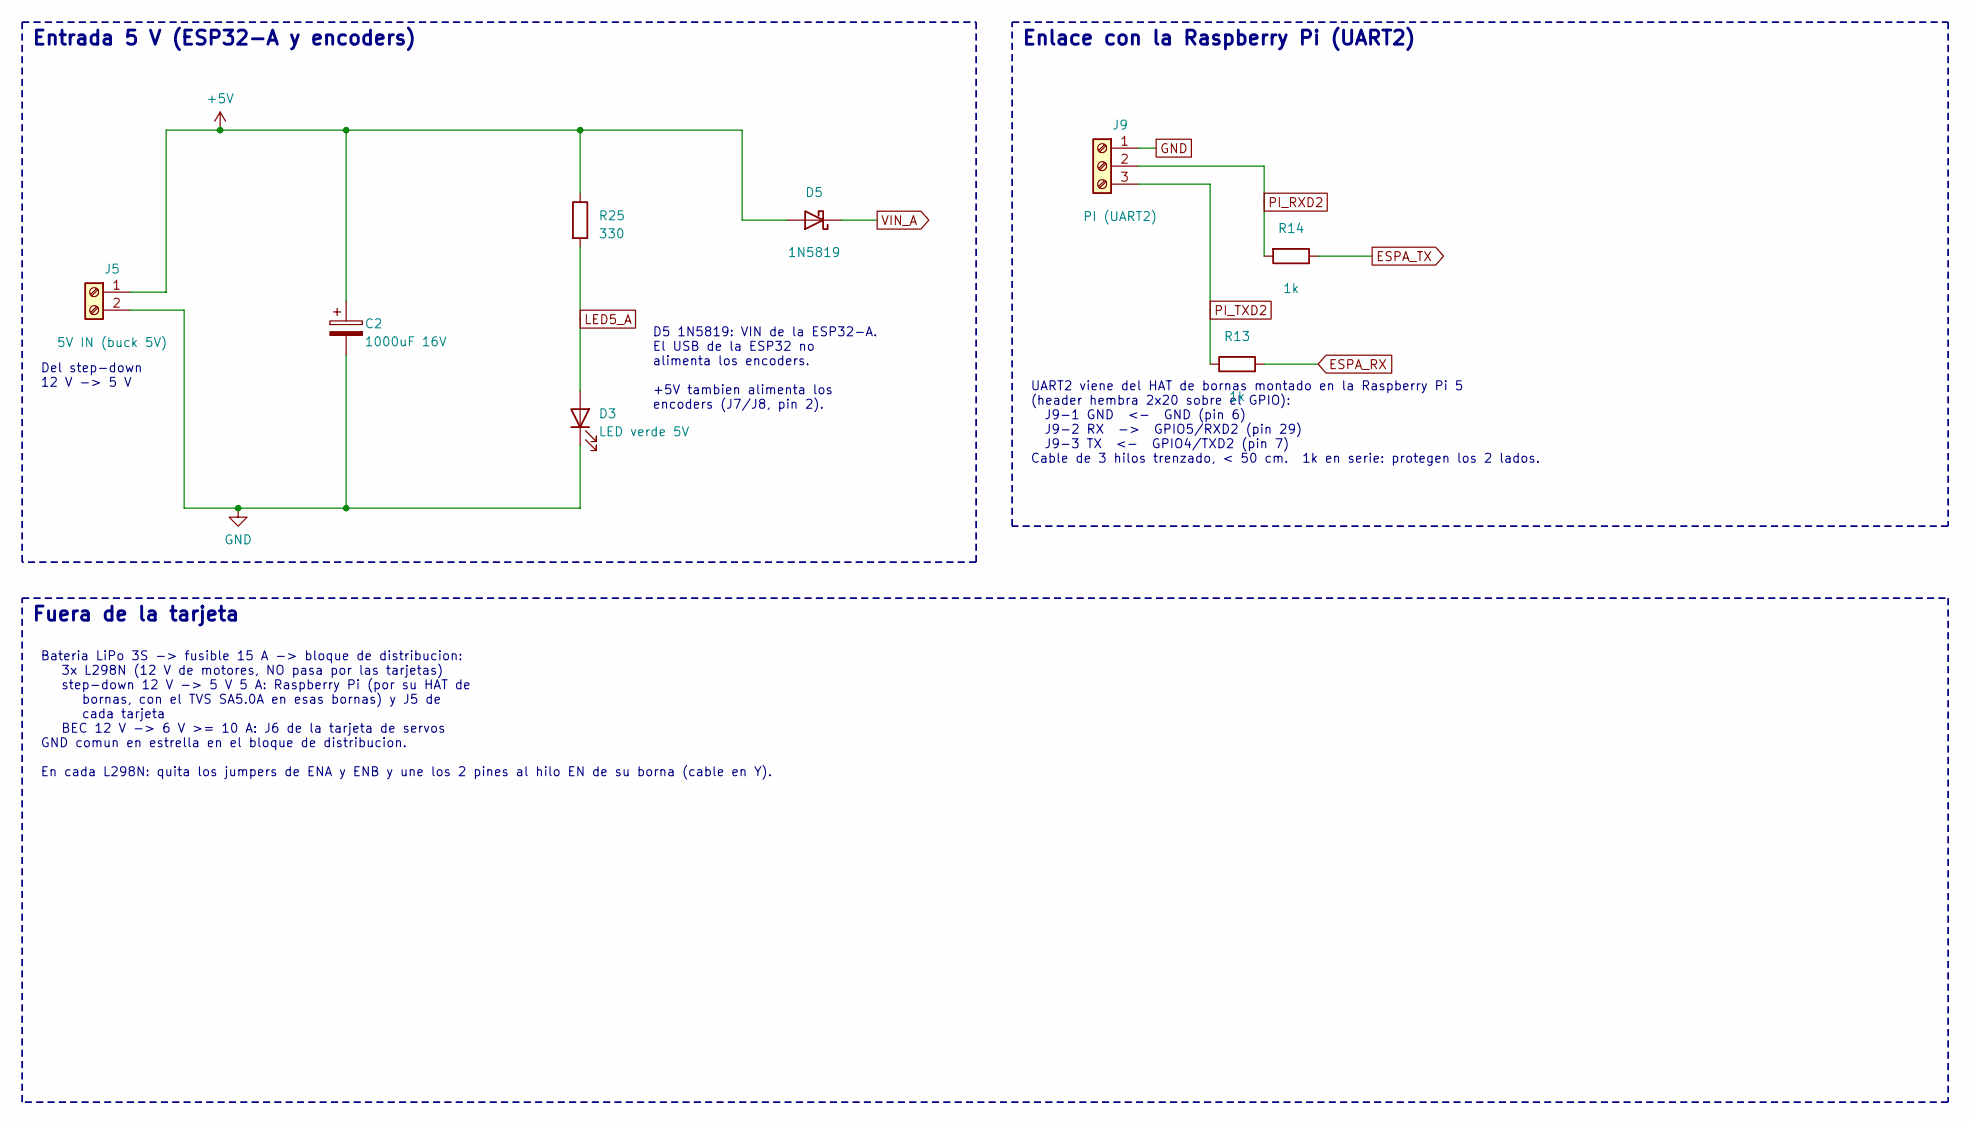
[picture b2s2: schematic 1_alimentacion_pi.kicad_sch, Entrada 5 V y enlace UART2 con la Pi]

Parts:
C2: 1000uF 16V; CP_Radial_D10.0mm_P5.00mm; MPN 1000uF 16V radial, cuerpo de 10 mm de d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
D3: LED verde 5V; LED_D5.0mm; MPN LED 5mm THT tradicional (verde)
D5: 1N5819; D_DO-41_SOD81_P10.16mm_Horizontal; MPN 1N5819 DO-41
J5: 5V IN (buck 5V); TerminalBlock_Phoenix_MKDS-1,5-2-5.08_1x02_P5.08mm_Horizont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; MPN Phoenix MKDS 1,5/2-5,08 o KF301-2P
J9: PI (UART2); TerminalBlock_Phoenix_PT-1,5-3-3.5-H_1x03_P3.50mm_Horizontal; MPN Phoenix PT 1,5/3-3,5-H o KF350-3P 3.5mm
R13, R14: 1k; R_Axial_DIN0207_L6.3mm_D2.5mm_P7.62mm_Horizontal; MPN Resistencia 1k 1/4W (0.25W) THT pelicul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
R25: 330; R_Axial_DIN0207_L6.3mm_D2.5mm_P7.62mm_Horizontal; MPN Resistencia 330 1/4W (0.25W) THT pelicu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

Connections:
+5V: C2.1, D5.2 (A), J5.1, R25.1; also elsewhere on the board
ESPA_RX: R13.2; also elsewhere on the board
ESPA_TX: R14.1; also elsewhere on the board
GND: C2.2, D3.1 (K), J5.2, J9.1; also elsewhere on the board
LED5_A: D3.2 (A), R25.2
PI_RXD2: J9.2, R14.2
PI_TXD2: J9.3, R13.1
VIN_A: D5.1 (K); also elsewhere on the board

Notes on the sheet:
Entrada 5 V (ESP32-A y encoders)
Del step-down 12 V -> 5 V
D5 1N5819: VIN de la ESP32-A. El USB de la ESP32 no alimenta los encoders. +5V tambien alimenta los encoders (J7/J8, pin 2).
Enlace con la Raspberry Pi (UART2)
UART2 viene del HAT de bornas montado en la Raspberry Pi 5 (header hembra 2x20 sobre el GPIO): J9-1 GND <- GND (pin 6) J9-2 RX -> GPIO5/RXD2 (pin 29) J9-3 TX <- GPIO4/TXD2 (pin 7) Cable de 3 hilos trenzado, < 50 cm. 1k en serie: protegen los 2 lados.
Fuera de la tarjeta
Bateria LiPo 3S -> fusible 15 A -> bloque de distribucion: 3x L298N (12 V de motores, NO pasa por las tarjetas) step-down 12 V -> 5 V 5 A: Raspberry Pi (por su HAT de bornas, con el TVS SA5.0A en esas bornas) y J5 de cada tarjeta BEC 12 V -> 6 V >= 10 A: J6 de la tarjeta de servos GND comun en estr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
